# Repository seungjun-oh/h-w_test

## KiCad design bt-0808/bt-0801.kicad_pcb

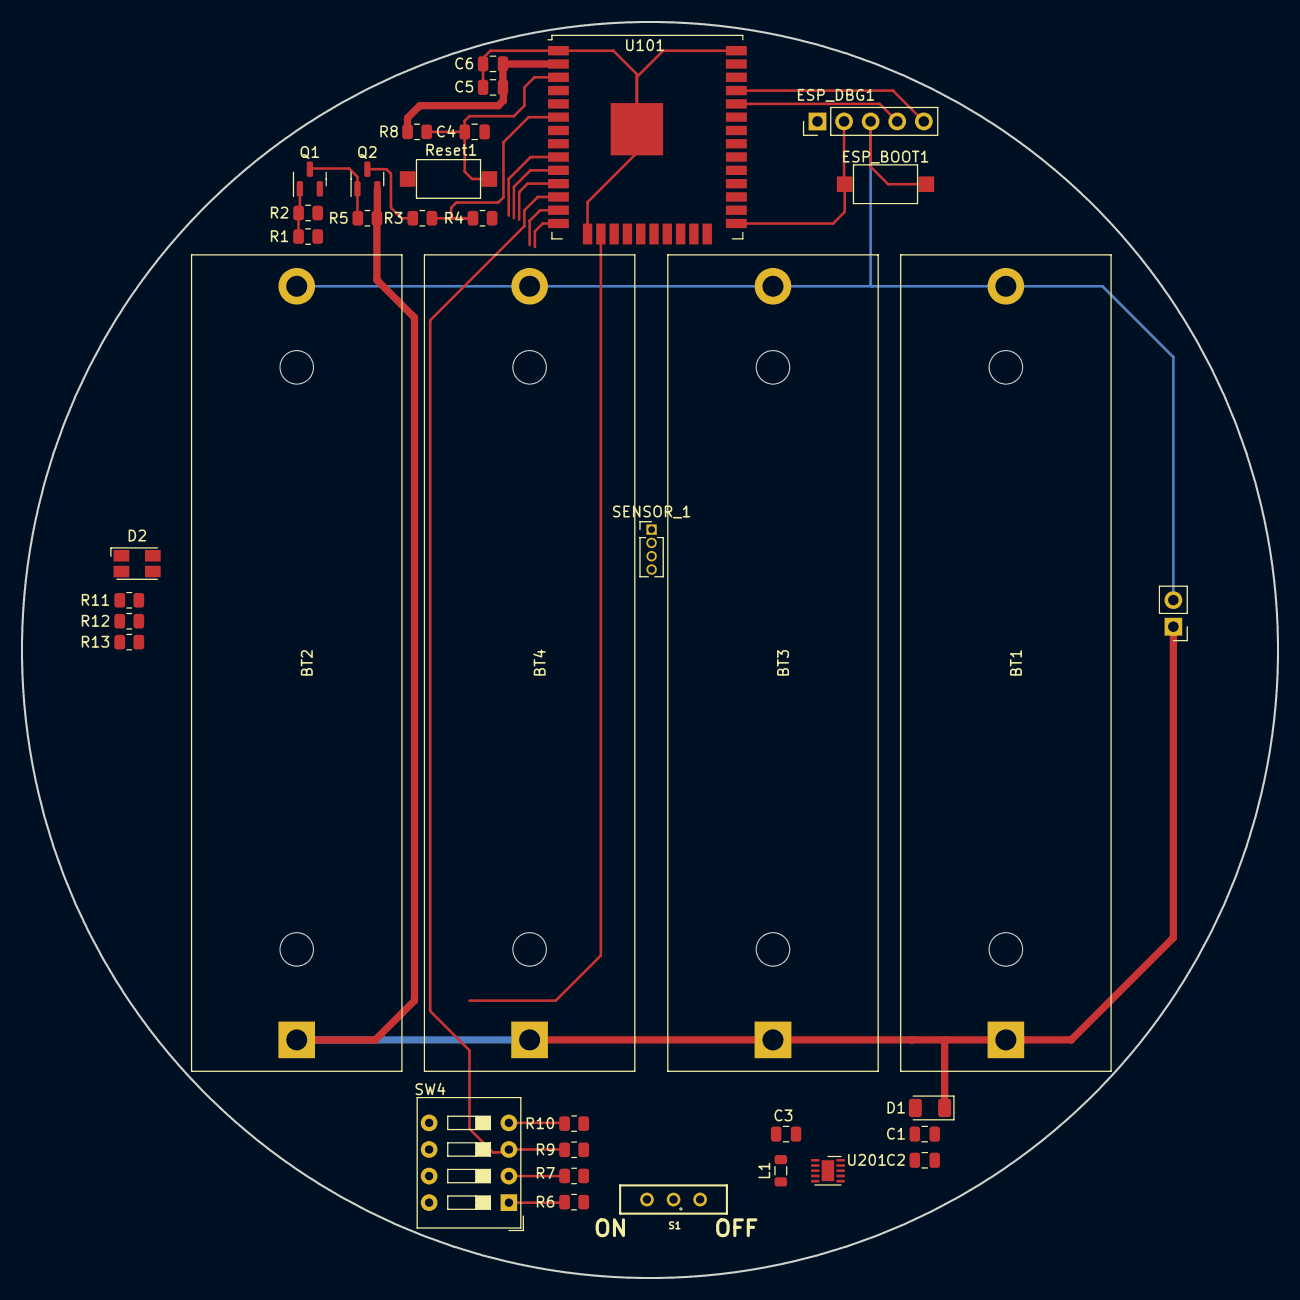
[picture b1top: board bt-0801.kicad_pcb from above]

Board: 2 copper layers, 120.0 x 120.0 mm, 37 parts (0 on the bottom side), 28 nets.

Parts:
BT1, BT2, BT3, BT4: 18650; BatteryHolder_MPD_BH-18650-PC2
C1, C2, C4, C5, C6: 100nF; C_0805_2012Metric
C3: 10uF/10v; C_0805_2012Metric
D1: DIODE; D_1206_3216Metric
D2: ASMB-MTB0-0A3A2; LED_Avago_PLCC4_3.2x2.8mm_CW
ESP_BOOT1: IT-1101NHA-180G; SW_SPST_CK_RS282G05A3
ESP_DBG1: SMW250-05; PinHeader_1x05_P2.54mm_Vertical
J2: PW; PinHeader_1x02_P2.54mm_Vertical
L1: INDUCTOR; L_0805_2012Metric
Q1: MMBT3904; SOT-23
Q2: IRLML6402; SOT-23
R1: 2K; R_0805_2012Metric
R2, R5, R6, R7, R8, R9, R10: 10K; R_0805_2012Metric
R3, R4: 10k; R_0805_2012Metric
R11, R12, R13: 270R; R_0805_2012Metric
Reset1: IT-1101NHA-180G; SW_SPST_CK_RS282G05A3
S1: 450301014042
SENSOR_1: 53047-0410; PinHeader_1x04_P1.27mm_Vertical
SW4: SW_DIP_x04; SW_DIP_SPSTx04_Slide_9.78x12.34mm_W7.62mm_P2.54mm
U101: ESP32-WROOM-32U
U201: TPS63030DSK; WSON-10-1EP_2.5x2.5mm_P0.5mm_EP1.2x2mm

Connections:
+3.3V: C5.1, C6.1, D2.1 (A), ESP_DBG1.1, R6.1, R7.1, R8.1, R9.1, R10.1, S1.2, SENSOR_1.1, U101.2 (VDD)
+BATT: BT1.1 (+), BT2.1 (+), BT3.1 (+), BT4.1 (+), D1.1 (A), J2.1, Q2.2 (S), R5.1
/+BAT_OUT: Q2.3 (D), R3.1
/BAT_CHECK: R3.2, R4.1, U101.6 (IO34)
/BAT_IN: R1.1, U101.29 (IO5)
/BOOT: ESP_BOOT1.1, ESP_DBG1.2, U101.25 (IO0)
/EN: C4.1, R8.2, Reset1.1, U101.3 (EN)
/FUNC_0: R6.2, SW4.1, U101.14 (IO12)
/FUNC_1: R7.2, SW4.2, U101.16 (IO13)
/FUNC_2: R9.2, SW4.3, U101.12 (IO27)
/FUNC_3: R10.2, SW4.4, U101.13 (IO14)
/LED_B: R13.1, U101.11 (IO26)
/LED_G: R12.1, U101.10 (IO25)
/LED_R: R11.2, U101.9 (IO33)
/RXD: ESP_DBG1.4, U101.34 (RXD0/IO3)
/SCL: SENSOR_1.3, U101.36 (IO22)
/SDA: SENSOR_1.2, U101.33 (IO21)
/TXD: ESP_DBG1.5, U101.35 (TXD0/IO1)
GND: BT1.2 (-), BT2.2 (-), BT3.2 (-), BT4.2 (-), C1.2, C2.2, C3.2, C4.2, C5.2, C6.2, ESP_BOOT1.2, ESP_DBG1.3, J2.2, Q1.2 (E), R2.2, R4.2, Reset1.2, SENSOR_1.4, SW4.5, SW4.6, SW4.7, SW4.8, U101.1 (GND), U101.15 (GND), U101.38 (GND), U101.39 (GND), U201.3 (PGND), U201.9 (GND), U201.11 (PGND)
unnamed: C1.1, C2.1, D1.2 (K), U201.5 (VIN), U201.6 (EN), U201.7 (PS/SYNC), U201.8 (VINA)
unnamed: C3.1, S1.1, U201.1 (VOUT), U201.10 (FB)
unnamed: D2.2 (BK), R13.2
unnamed: D2.3 (GK), R12.2
unnamed: D2.4 (RK), R11.1
unnamed: L1.1, U201.4 (L1)
unnamed: L1.2, U201.2 (L2)
unnamed: Q1.1 (B), R1.2, R2.1
unnamed: Q1.3 (C), Q2.1 (G), R5.2

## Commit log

2022-08-02 new_18
2022-08-02 fix : add name.
2022-08-03 altium_28
2022-08-08 nosi
2022-08-08 0808newfile
2022-08-08 imagefile_add
2022-08-08 pcb_update
2022-08-08 test_new_line
2022-08-09 각부품값수정
